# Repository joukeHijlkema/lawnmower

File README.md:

# lawnmower
A GPS controled lawn mowing robot project

Just starting, give me some time to get it together

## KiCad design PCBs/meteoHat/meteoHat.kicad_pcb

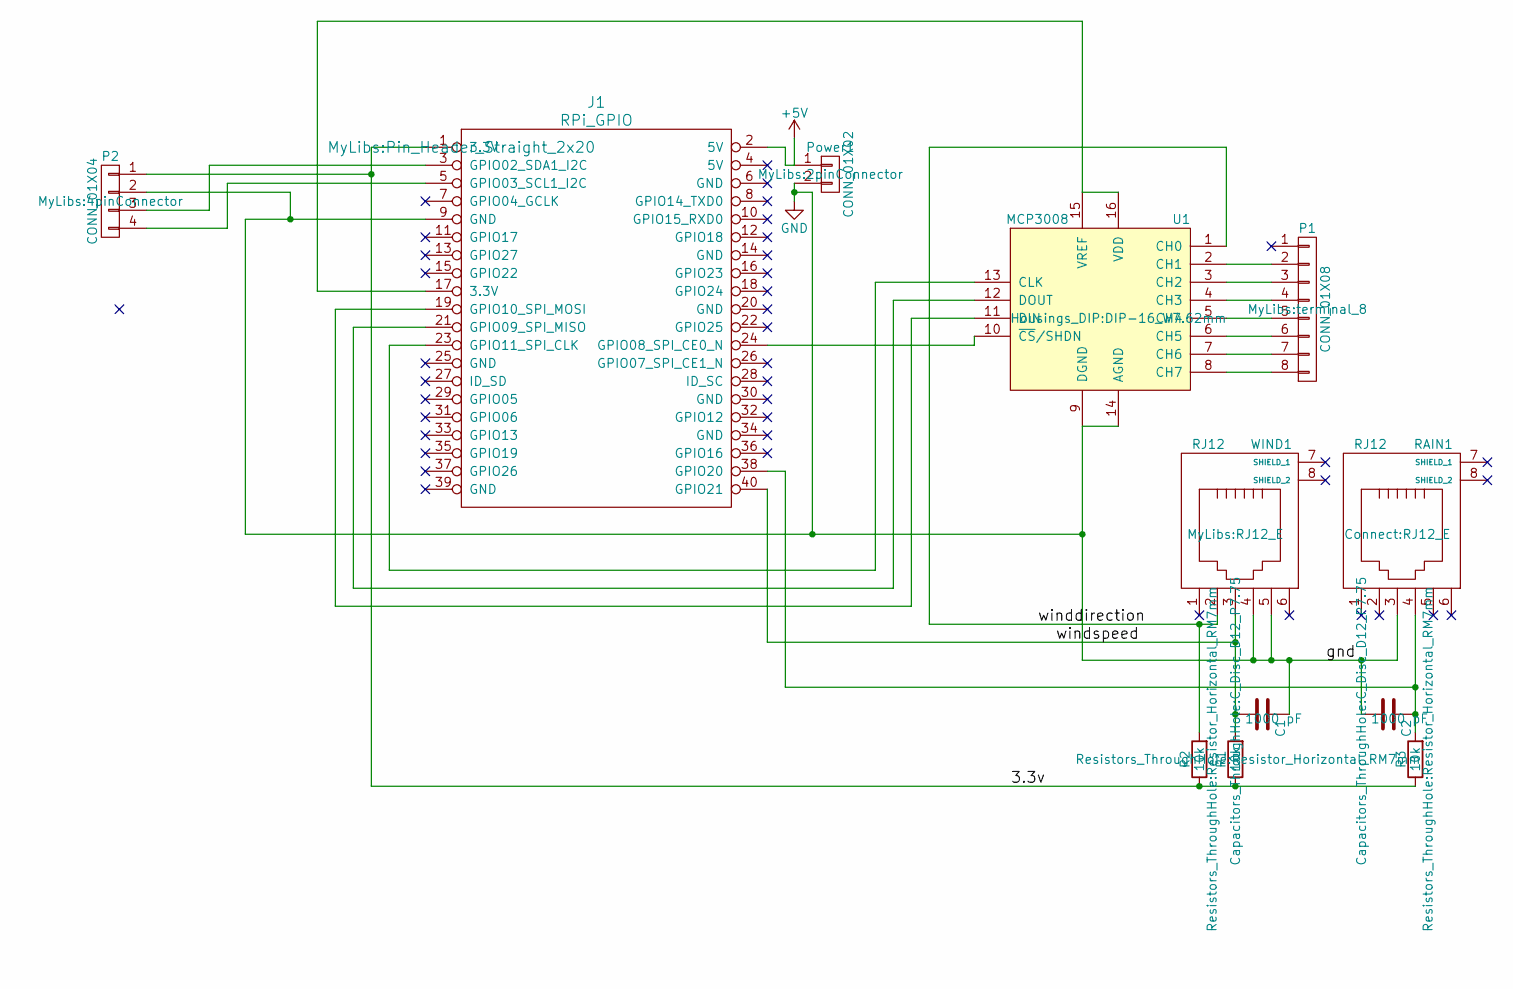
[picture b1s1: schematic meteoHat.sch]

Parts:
C1, C2: 1000 pF; C_Disc_D12_P7.75
J1: RPi_GPIO; Pin_Header_Straight_2x20
P1: CONN_01X08; terminal_8
P2: CONN_01X04; 4pinConnector
Power1: CONN_01X02; 2pinConnector
R1, R2, R3: 10k; Resistor_Horizontal_RM7mm
RAIN1: RJ12; RJ12_E
U1: MCP3008; DIP-16_W7.62mm
WIND1: RJ12; RJ12_E

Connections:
+5V: J1.2 (5V), Power1.1
/3.3v: J1.1 (3.3V), P2.1, R1.1, R2.1, R3.1
/winddirection: R2.2, U1.1 (CH0), WIND1.2
/windspeed: C1.2, J1.40 (GPIO21), R1.2, WIND1.3
GND: C1.1, C2.2, J1.9 (GND), P2.2, Power1.2, RAIN1.3, U1.9 (DGND), U1.14 (AGND), WIND1.4, WIND1.5
unnamed: C2.1, J1.38 (GPIO20), R3.2, RAIN1.4
unnamed: J1.3 (GPIO02_SDA1_I2C), P2.3
unnamed: J1.5 (GPIO03_SCL1_I2C), P2.4
unnamed: J1.17 (3.3V), U1.15 (VREF), U1.16 (VDD)
unnamed: J1.19 (GPIO10_SPI_MOSI), U1.11 (DIN)
unnamed: J1.21 (GPIO09_SPI_MISO), U1.12 (DOUT)
unnamed: J1.23 (GPIO11_SPI_CLK), U1.13 (CLK)
unnamed: J1.24 (GPIO08_SPI_CE0_N), U1.10 (~CS~/SHDN)
unnamed: P1.2, U1.2 (CH1)
unnamed: P1.3, U1.3 (CH2)
unnamed: P1.4, U1.4 (CH3)
unnamed: P1.5, U1.5 (CH4)
unnamed: P1.6, U1.6 (CH5)
unnamed: P1.7, U1.7 (CH6)
unnamed: P1.8, U1.8 (CH7)

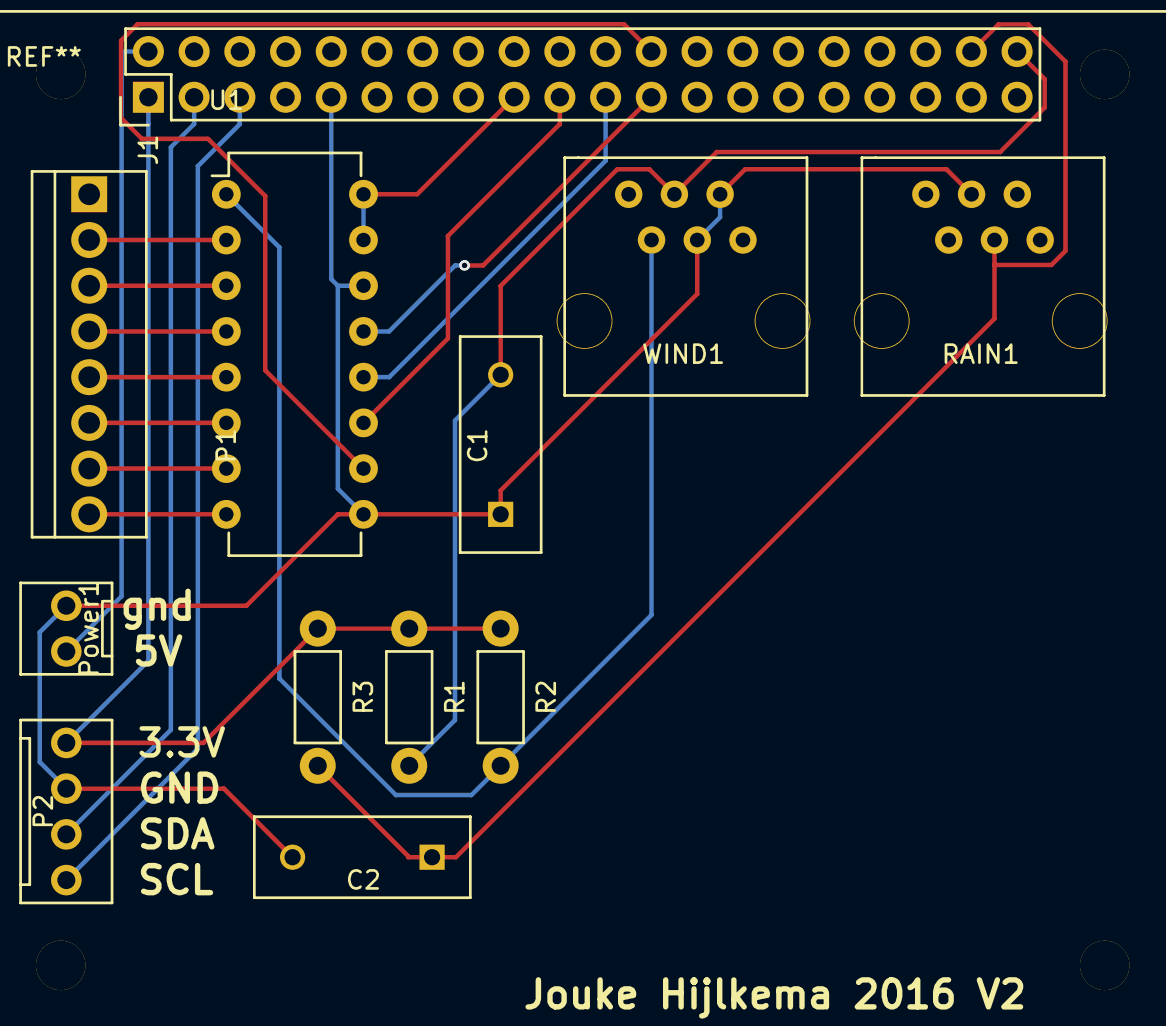
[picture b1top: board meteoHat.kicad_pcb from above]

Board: 2 copper layers, 12 parts (0 on the bottom side), 20 nets.

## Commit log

2016-01-27 test
2016-01-27 actual state of the C++ code. Moving to github
2016-01-27 actual state of the Java code. Moving to github
2016-01-27 actual state of the Tools. Moving to github
2016-01-27 move to github
2016-01-30 fixed sync
2016-01-31 Plans for the PCBs
2016-03-09 added drawings and PCBs
2016-04-07 added PCBs
2016-04-08 Meteo website stuff
2016-04-08 Meteo website stuff, forgot backdrop
2016-05-12 moved designs to mega
2017-02-03 added drawings
2017-03-12 removed meteo from this project ... nothing to do here
2017-06-23 new drawings
